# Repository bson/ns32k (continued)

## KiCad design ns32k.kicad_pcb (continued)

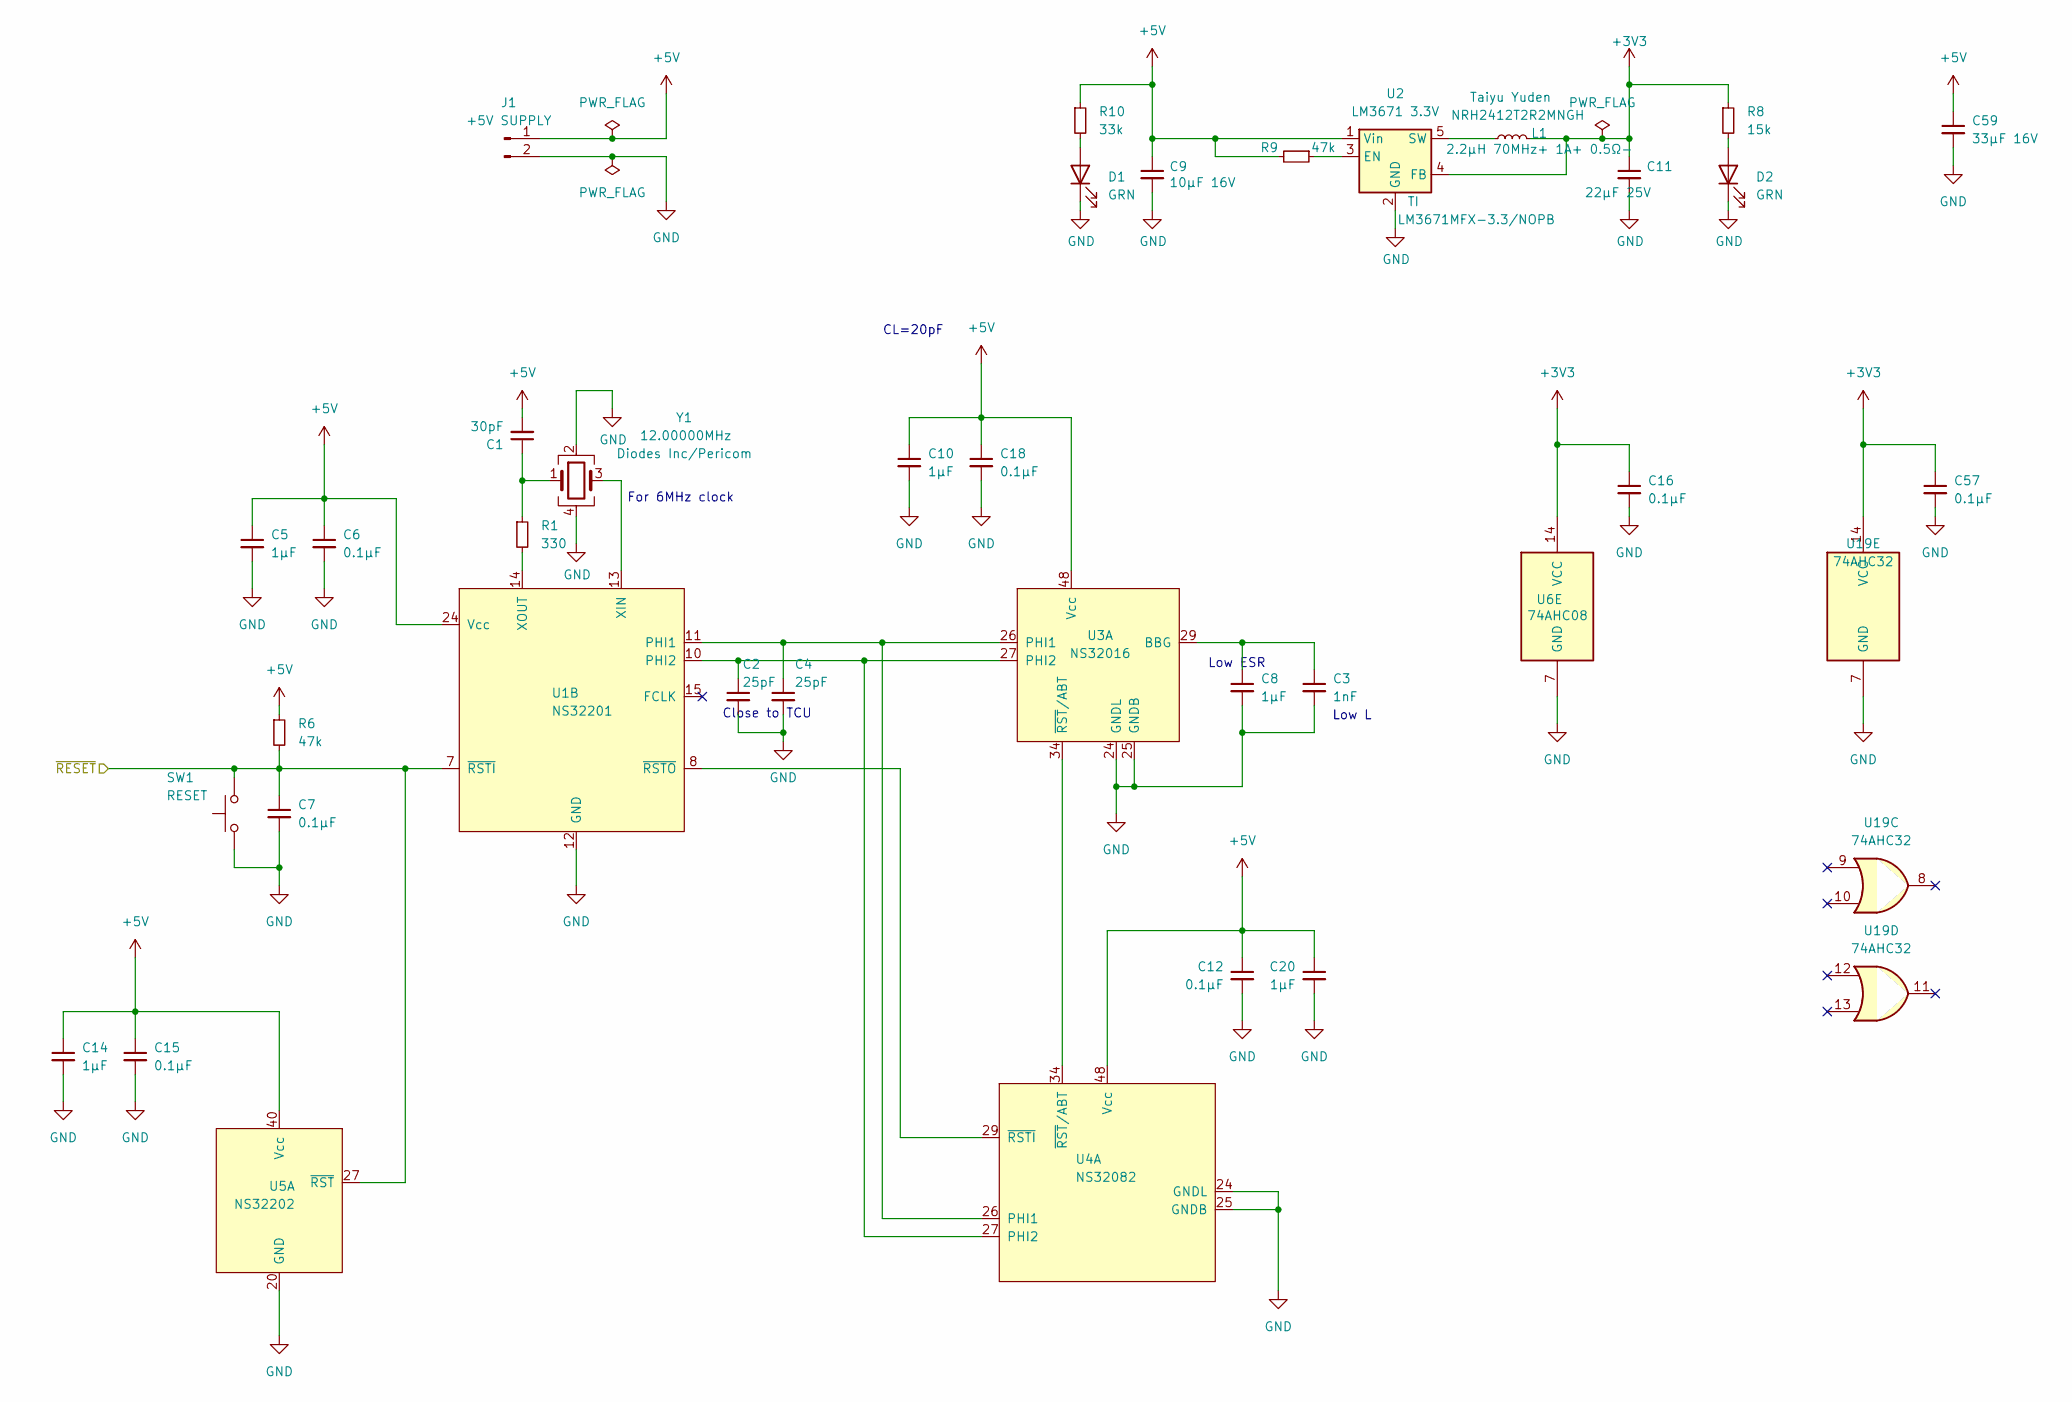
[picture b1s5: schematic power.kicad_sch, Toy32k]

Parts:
C1: 30pF; C_0402_1005Metric; LCSC C312063
C2, C4: 25pF; C_0402_1005Metric; LCSC C696895
C3: 1nF; C_0402_1005Metric; LCSC C696895
C5, C8, C10, C14, C20: 1µF; C_0603_1608Metric; LCSC C5189821
C6, C7, C12, C15, C16, C18, C57: 0.1µF; C_0402_1005Metric; LCSC C3012376
C9: 10µF 16V; C_0603_1608Metric; LCSC C109457
C11: 22µF 25V; C_0805_2012Metric; LCSC C258782
C59: 33µF 16V; C_1206_3216Metric; LCSC C342606
D1, D2: GRN; D_0603_1608Metric; LCSC C5246833
J1: +5V SUPPLY; PinHeader_1x02_P2.54mm_Vertical
L1: 2.2µH 70MHz+ 1A+ 0.5Ω-; L_Taiyo-Yuden_NR-24xx; Part NRH2412T2R2MNGH
R1: 330; R_0402_1005Metric; LCSC C186314
R6: 47k; R_0402_1005Metric; LCSC C139047
R8: 15k; R_0402_1005Metric; LCSC C850820
R9: 47k; R_0402_1005Metric; LCSC C3017507
R10: 33k; R_0402_1005Metric; LCSC C2906928
SW1: RESET; SW_SPST_CK_RS282G05A3
U1: NS32201; DIP-24_W15.24mm_Socket
U2: LM3671 3.3V; TSOT-23-5; Part LM3671MFX-3.3/NOPB; LCSC C201586
U3: NS32016; DIP-48_W15.24mm_Socket
U4: NS32082; DIP-48_W15.24mm_Socket
U5: NS32202; DIP-40_W15.24mm_Socket
U6: 74AHC08; TSSOP-14_4.4x5mm_P0.65mm; LCSC C842279
U19: 74AHC32; TSSOP-14_4.4x5mm_P0.65mm; LCSC C2868909
Y1: 12.00000MHz; FH12000001; LCSC C7294547

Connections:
+3V3: C11.1, C16.1, C57.1, L1.2, R8.1, U2.4 (FB), U6.14 (VCC), U19.14 (VCC); also elsewhere on the board
+5V: C1.2, C5.1, C6.1, C9.1, C10.1, C12.1, C14.1, C15.1, C18.1, C20.1, C59.1, J1.1, R6.1, R9.2, R10.1, U1.24 (Vcc), U2.1 (Vin), U3.48 (Vcc), U4.48 (Vcc), U5.40 (Vcc); also elsewhere on the board
/Ethernet/~RESET: C7.1, R6.2, SW1.1, U1.7 (~RSTI), U5.27 (~RST); also elsewhere on the board
GND: C2.2, C3.2, C4.2, C5.2, C6.2, C7.2, C8.2, C9.2, C10.2, C11.2, C12.2, C14.2, C15.2, C16.2, C18.2, C20.2, C57.2, C59.2, D1.1 (K), D2.1 (K), J1.2, SW1.2, U1.12 (GND), U2.2 (GND), U3.24 (GNDL), U3.25 (GNDB), U4.24 (GNDL), U4.25 (GNDB), U5.20 (GND), U6.7 (GND), U19.7 (GND), Y1.2, Y1.4; also elsewhere on the board
unnamed: C1.1, R1.1, Y1.1
unnamed: D1.2 (A), R10.2
unnamed: D2.2 (A), R8.2
unnamed: C4.1, U1.11 (PHI1), U3.26 (PHI1), U4.26 (PHI1)
unnamed: C2.1, U1.10 (PHI2), U3.27 (PHI2), U4.27 (PHI2)
unnamed: U1.13 (XIN), Y1.3
unnamed: R1.2, U1.14 (XOUT)
unnamed: U1.8 (~RSTO), U4.29 (~RSTI)
unnamed: R9.1, U2.3 (EN)
unnamed: L1.1, U2.5 (SW)
unnamed: C3.1, C8.1, U3.29 (BBG)
unnamed: U3.34 (~RST/ABT), U4.34 (~RST/ABT)

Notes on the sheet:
Low L
For 6MHz clock
CL=20pF
Close to TCU
Low ESR

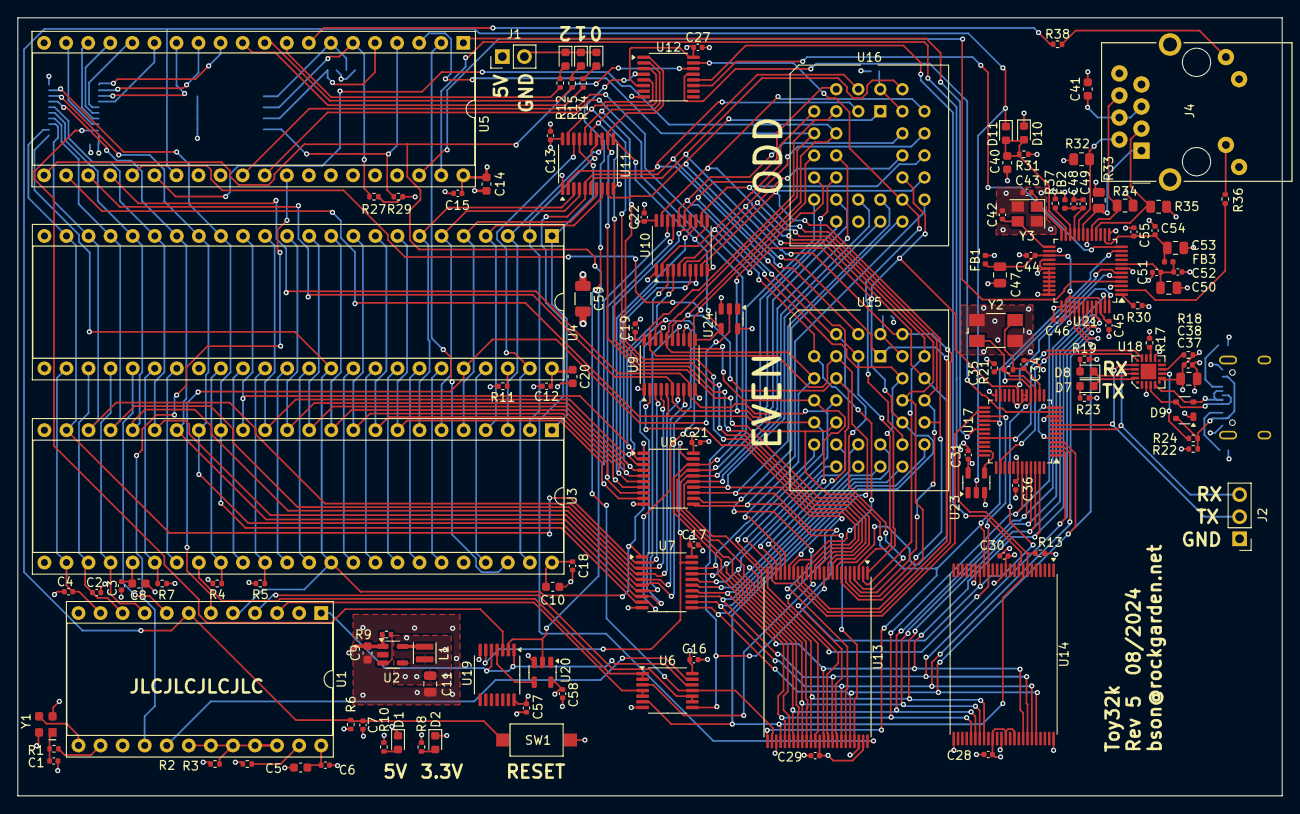
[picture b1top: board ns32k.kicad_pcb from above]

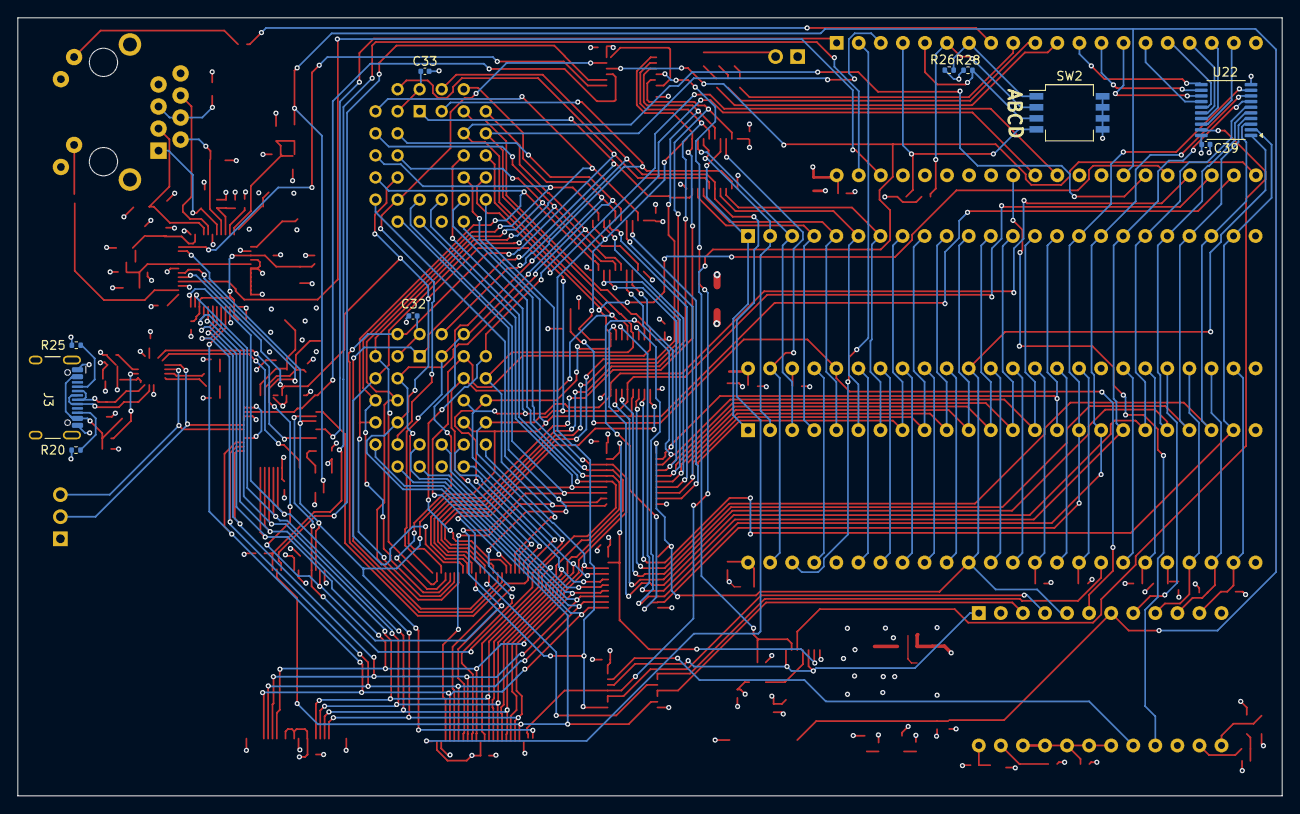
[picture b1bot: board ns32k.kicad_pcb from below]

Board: 4 copper layers, 145.5 x 89.6 mm, 138 parts (10 on the bottom side), 176 nets.

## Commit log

2024-07-24 initial commit; as sent to JLCPCB for Rev 1
2024-07-24 add datasheets
2024-07-24 Add Changelist/TODO
2024-07-24 Add RAM symbol file
2024-07-24 add ibom output
2024-07-25 add NS32k manuals
2024-07-25 add ICU int ack decoding
2024-07-25 move ICU# delay to after decode
2024-07-25 add datasheet for 74AHC1G08
2024-07-25 fix VUSB bug
2024-07-25 add reset button
2024-07-25 cleanups, DRC
2024-07-26 add ethernet to schematic
2024-07-26 fix DRC errors, add RJ45 step model
2024-07-26 save unsaved changed
2024-07-27 route ethernet, reroute USB
2024-07-27 correct datasheet, update 4148 footprint from 0805 to 0603
2024-07-27 set USB-C 3D model
2024-07-27 cosmetic changes
2024-07-27 add 0R's to ICU CS logic
2024-07-27 use ICU even pins for GPIO
2024-07-27 add jumpers, much cleanup
2024-07-27 add ~* to .gitignore
2024-07-27 add buffer to ICU
2024-07-27 layout ICU buffering
2024-07-27 cleanups
2024-07-27 remove datasheet for unused part
2024-07-28 add TI PW footprint drawing
2024-07-28 add 33uF 1206 16V reservoir cap to 5V
2024-07-28 generate Rev 2 gerbers
2024-07-28 update rev2 gerbers
2024-07-28 add ibom for rev2
2024-07-30 fix ICU addressing error
2024-07-30 Rev3 gerbers
2024-08-01 Rework RESET/RST: see Changelist
2024-08-01 mark even/odd ROM banks
2024-08-01 fix reset timing, should be 100us, not 100ms...
2024-08-01 update text to say rev 4
2024-08-02 Power ICU AHC245 buffer with +5V
2024-08-03 add pullup to NAND R/B# as per ONFI 1.0 spec
2024-08-05 save drc exclusions
2024-08-05 updated ibom
2024-08-10 update dnps
2024-08-10 update value of 49.9 ethernet resistors to reflect 1/4 W
2024-08-11 fix address decoding
2024-08-11 add rev4 gerbers, bom files
2024-08-12 various changes, add LCSC part #s
2024-08-12 revert crystal footprints back from LCSC parts
2024-08-12 update gerbers
2024-08-12 update Changelist
2024-08-12 update Changelist to reflect rev4
2024-08-13 restore L1 TY NHR24xx FP
2024-08-16 rev4 errata, fix in main
2024-08-17 update Changelist with 16550 AS error
2024-08-17 AS is active high, and we tie it to GND
2024-08-17 Chanelist
2024-08-17 fix a few bugs
2024-08-19 save changes
2024-08-19 fix UART addressing, generate gerbers
2024-08-20 save exclusions
2024-08-25 add rev5 ibom
2024-08-29 add finer JLCPCB tolerances
